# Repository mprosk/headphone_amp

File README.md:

# headphone_amp
Compact headphone output module based on the LM4808

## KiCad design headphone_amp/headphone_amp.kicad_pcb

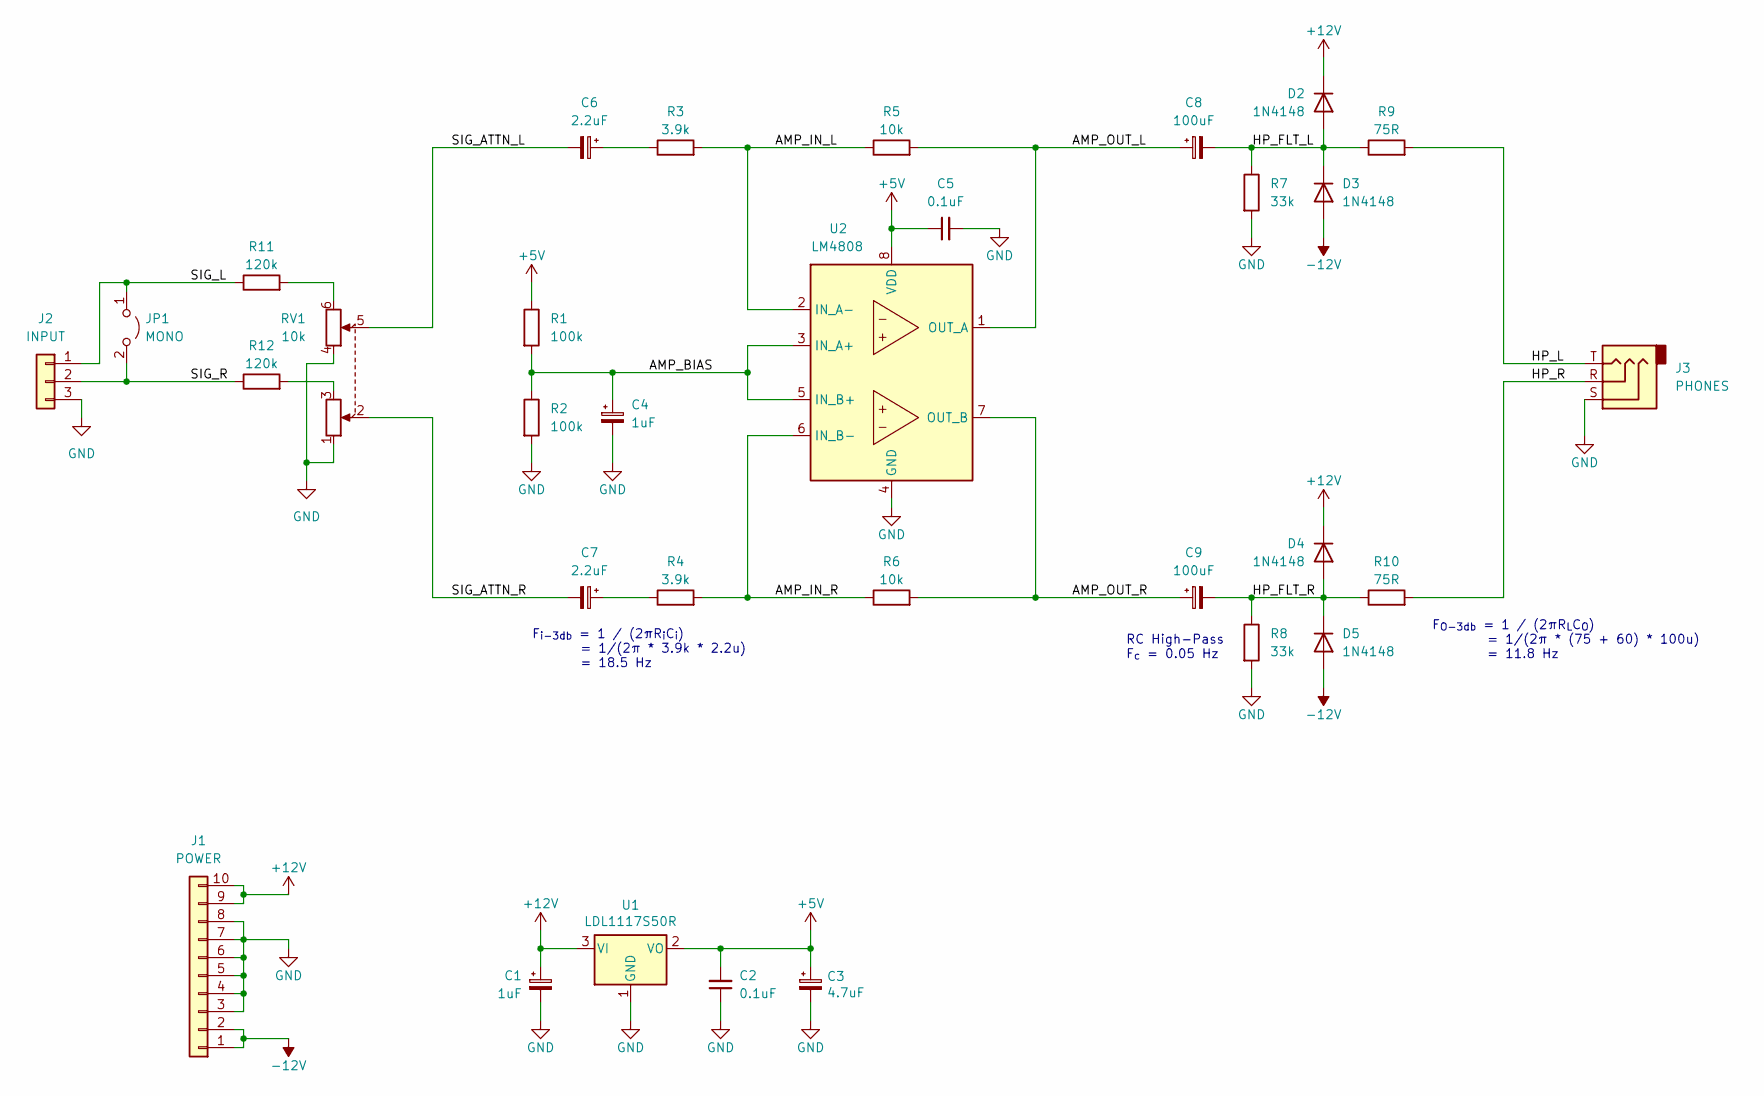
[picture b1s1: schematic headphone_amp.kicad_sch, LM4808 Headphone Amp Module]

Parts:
C1, C4: 1uF; CP_Radial_D5.0mm_P2.00mm
C2, C5: 0.1uF; C_Disc_D3.0mm_W1.6mm_P2.50mm
C3: 4.7uF; CP_Radial_D5.0mm_P2.00mm
C6, C7: 2.2uF; CP_Radial_D5.0mm_P2.00mm
C8, C9: 100uF; CP_Radial_D5.0mm_P2.50mm
D2, D3, D4, D5: 1N4148; D_DO-34_SOD68_P7.62mm_Horizontal
J1: POWER; IDC-Header_2x05_P2.54mm_Vertical
J2: INPUT; Molex_KK-254_AE-6410-03A_1x03_P2.54mm_Vertical
J3: PHONES; Molex_KK-254_AE-6410-03A_1x03_P2.54mm_Vertical
JP1: MONO; PinHeader_1x02_P2.54mm_Vertical
R1, R2: 100k; R_Axial_DIN0207_L6.3mm_D2.5mm_P10.16mm_Horizontal
R3, R4: 3.9k; R_Axial_DIN0207_L6.3mm_D2.5mm_P10.16mm_Horizontal
R5, R6: 10k; R_Axial_DIN0207_L6.3mm_D2.5mm_P10.16mm_Horizontal
R7, R8: 33k; R_Axial_DIN0207_L6.3mm_D2.5mm_P10.16mm_Horizontal
R9, R10: 75R; R_Axial_DIN0207_L6.3mm_D2.5mm_P10.16mm_Horizontal
R11, R12: 120k; R_Axial_DIN0207_L6.3mm_D2.5mm_P10.16mm_Horizontal
RV1: 10k; Pot_Bourns_PTD902
U1: LDL1117S50R; SOT-223-3_TabPin2
U2: LM4808; SOIC-8_3.9x4.9mm_P1.27mm

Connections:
+5V: C2.2, C3.1, C5.1, R1.1, U1.2 (VO), U2.8 (VDD)
+12V: C1.1, D2.1 (K), D4.1 (K), J1.9, J1.10, U1.3 (VI)
-12V: D3.2 (A), D5.2 (A), J1.1, J1.2
/AMP_BIAS: C4.1, R1.2, R2.1, U2.3 (IN_A+), U2.5 (IN_B+)
/AMP_IN_L: R3.2, R5.1, U2.2 (IN_A-)
/AMP_IN_R: R4.2, R6.1, U2.6 (IN_B-)
/AMP_OUT_L: C8.1, R5.2, U2.1 (OUT_A)
/AMP_OUT_R: C9.1, R6.2, U2.7 (OUT_B)
/HP_FLT_L: C8.2, D2.2 (A), D3.1 (K), R7.1, R9.1
/HP_FLT_R: C9.2, D4.2 (A), D5.1 (K), R8.1, R10.1
/HP_L: J3.T, R9.2
/HP_R: J3.R, R10.2
/SIG_ATTN_L: C6.2, RV1.5
/SIG_ATTN_R: C7.2, RV1.2
/SIG_L: J2.1, JP1.1 (A), R11.1
/SIG_R: J2.2, JP1.2 (B), R12.1
GND: C1.2, C2.1, C3.2, C4.2, C5.2, J1.3, J1.4, J1.5, J1.6, J1.7, J1.8, J2.3, J3.S, R2.2, R7.2, R8.2, RV1.1, RV1.4, U1.1 (GND), U2.4 (GND)
unnamed: C6.1, R3.1
unnamed: C7.1, R4.1
unnamed: R11.2, RV1.6
unnamed: R12.2, RV1.3

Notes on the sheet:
F_{i-3db} = 1 / (2πR_{i}C_{i}) = 1/(2π * 3.9k * 2.2u) = 18.5 Hz
F_{O-3db} = 1 / (2πR_{L}C_{O}) = 1/(2π * (75 + 60) * 100u) = 11.8 Hz
RC High-Pass F_{c} = 0.05 Hz

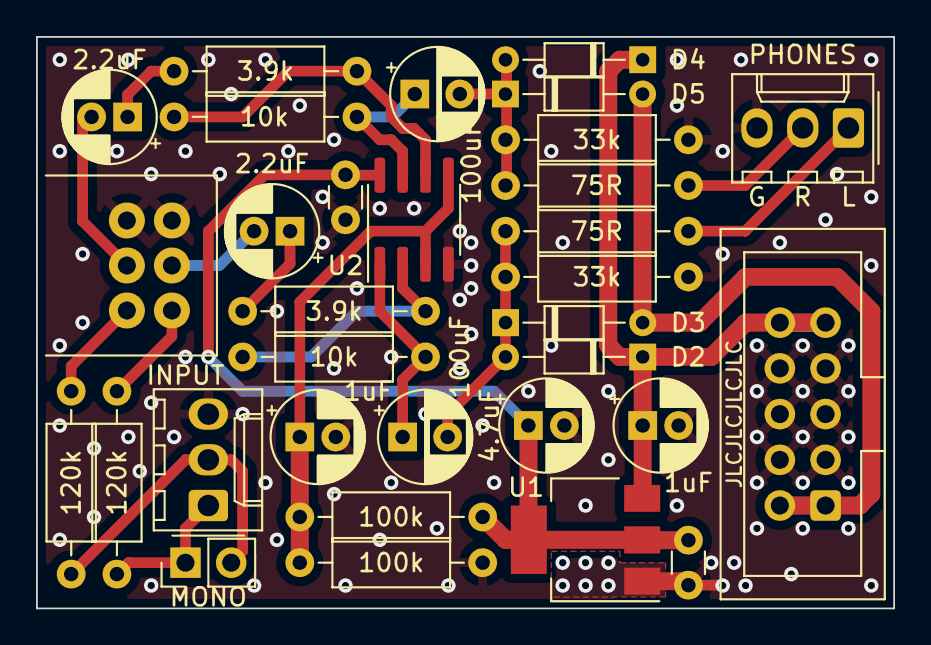
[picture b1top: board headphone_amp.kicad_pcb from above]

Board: 2 copper layers, 47.6 x 31.8 mm, 32 parts (0 on the bottom side), 21 nets.

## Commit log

2022-05-28 Copy local files into repo
2022-05-30 Finish silkscreen. Reexport gerbers
2022-05-30 Use kosmo-lib. Export PDF
2022-06-04 Move kosmo-lib into subfolder
2022-06-04 Add mono jumper
